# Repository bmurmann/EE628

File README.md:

# EE 628 (University of Hawaiʻi at Mānoa)

### Analysis and Design of Integrated Circuits

Learn mixed-signal circuit design using open-source tools and create your own voltmeter chip!

This course is being developed in collaboration with the Microelectronics Commons [California-Pacific-Northwest AI Hub](https://microelectronicscommons.org/connect/california-pacific-northwest-ai-hardware-hub-northwest-ai-hub/).

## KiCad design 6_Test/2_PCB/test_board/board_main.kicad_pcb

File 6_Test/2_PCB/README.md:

This folder contains all files related to PCB design and test setup.

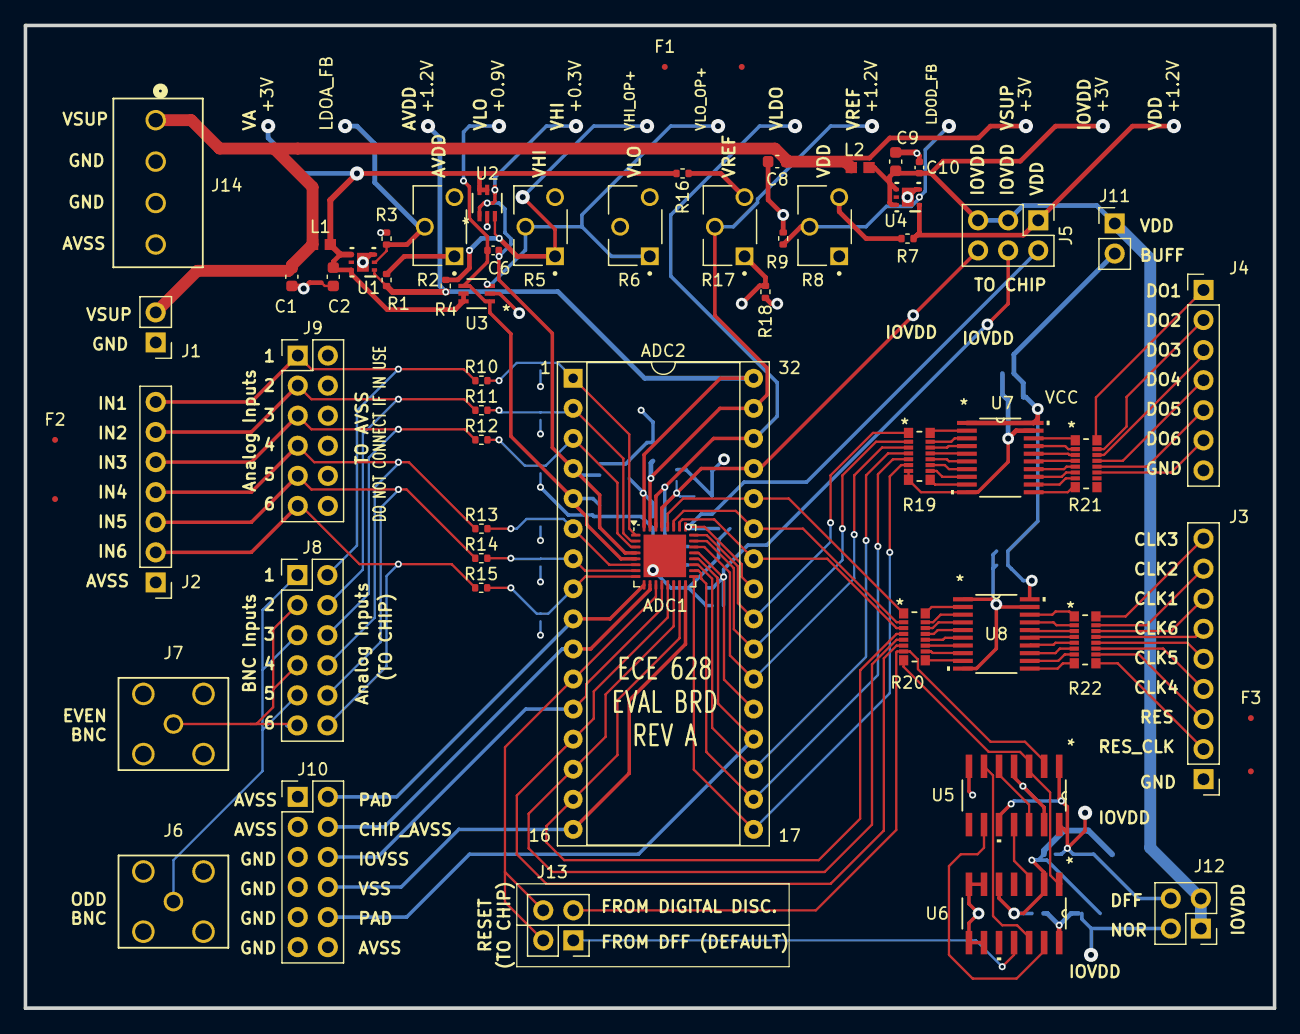
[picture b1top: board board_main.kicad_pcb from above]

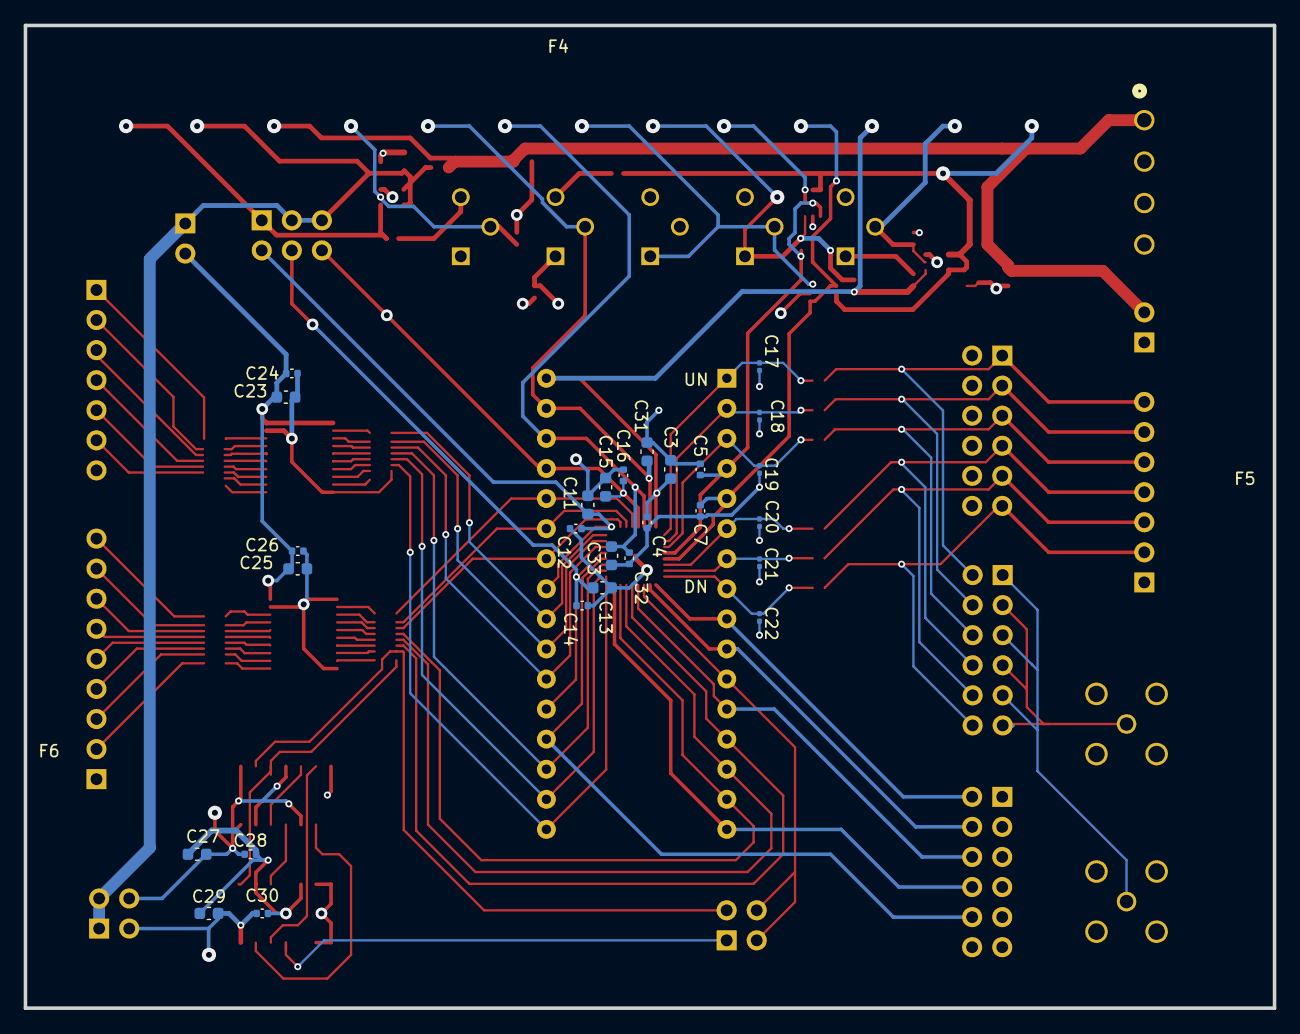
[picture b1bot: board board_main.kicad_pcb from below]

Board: 4 copper layers, 105.5 x 83.0 mm, 87 parts (27 on the bottom side), 110 nets.

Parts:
ADC1: ADC_Chip; QFN-32-1EP_5x5mm_P0.5mm_EP3.6x3.6mm
ADC2: ADC_Socket; DIP-32_W15.24mm_Socket
C1, C2, C3, C8, C9, C11, C13, C15, C23, C25, C27, C29, C31, C33: 4.7u; C_0603_1608Metric
C4, C5, C6, C7, C10, C12, C14, C16, C24, C26, C28, C30, C32: 100n; C_0402_1005Metric
C17, C18, C19, C20, C21, C22: 100pF; C_0201_0603Metric
F1, F2, F3, F4, F5, F6: Fiducial_0.5mm_Mask1.5mm
J1: PWR_Supply_Pins; PinHeader_1x02_P2.54mm_Vertical
J2: Analog_Input_Pins; PinHeader_1x07_P2.54mm_Vertical
J3: Digital_Input_Pins; PinHeader_1x09_P2.54mm_Vertical
J4: Digital_Output_Pins; PinHeader_1x07_P2.54mm_Vertical
J5: Chip_VDD_Jumpers; PinHeader_2x03_P2.54mm_Vertical
J6: BNC_Odd; bnc_mini_gnd
J7: BNC_Even; bnc_mini_gnd
J8: BNC_Jumpers; PinHeader_2x06_P2.54mm_Vertical
J9: Analog_Input_Jumpers; PinHeader_2x06_P2.54mm_Vertical
J10: Chip_AVSS_GND_Jumpers; PinHeader_2x06_P2.54mm_Vertical
J11: Buffer_PWR_Jumper; PinHeader_1x02_P2.54mm_Vertical
J12: Reset_PWR_Jumpers; PinHeader_2x02_P2.54mm_Vertical
J13: Reset_Signal_Jumpers; PinHeader_2x02_P2.54mm_Vertical
J14: 1546551-4; CONN4_1546551-4_TEC
L1, L2: BLM18PG121SN1D; IND_BLM18_0603_MUR
R1, R4, R7, R10, R11, R12, R13, R14, R15: 1k; R_0402_1005Metric
R2, R5, R6, R8, R17: 10k; potentiometer_10turn
R3: r=4.7k; R_0402_1005Metric
R9, R16, R18: 4.7k; R_0402_1005Metric
R19, R20, R21, R22: EXB-2HV220JV; RES_EXB2HV
U1, U4: TPS74501PDRVR; DRV0006A_NV
U2, U3: ADA4807-1AKSZ-R7; KS-6_ADI
U5: SN74HC74DR; flip_flop_D14
U6: CD4001BM96; nor_gate_D14
U7, U8: SN74LVC245APWR; PW20

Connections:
/ADC/AVDD: ADC1.32 (AVDD), ADC2.32 (AVDD), C3.1, C4.2, R1.1, R4.1, U1.1 (OUT)
/ADC/AVSS: C3.2, C4.1, C5.1, C7.1, C17.2, C18.2, C19.2, C20.2, C21.2, C22.2, C31.2, C32.2, C33.2, J2.1, J6.2 (AVSS1), J6.3 (AVSS2), J6.4 (AVSS3), J6.5 (AVSS4), J7.2 (AVSS1), J7.3 (AVSS2), J7.4 (AVSS3), J7.5 (AVSS4), J9.B1, J9.B2, J9.B3, J9.B4, J9.B5, J9.B6, J10.A1, J10.A2, J10.B6, J14.4, R3.1, R6.2, R18.2
/ADC/CK1: ADC1.26 (CK1), ADC2.26 (CK1), R20.3
/ADC/CK2: ADC1.27 (CK2), ADC2.27 (CK2), R20.2
/ADC/CK3: ADC1.28 (CK3), ADC2.28 (CK3), R20.1
/ADC/CK4: ADC1.13 (CK4), ADC2.13 (CK4), R20.6
/ADC/CK5: ADC1.14 (CK5), ADC2.14 (CK5), R20.5
/ADC/CK6: ADC1.15 (CK6), ADC2.15 (CK6), R20.4
/ADC/IN1: J2.7, J8.B1, J9.A1, R10.1
/ADC/IN2: J2.6, J8.B2, J9.A2, R11.1
/ADC/IN3: J2.5, J8.B3, J9.A3, R12.1
/ADC/IN4: J2.4, J8.B4, J9.A4, R13.1
/ADC/IN5: J2.3, J8.B5, J9.A5, R14.1
/ADC/IN6: J2.2, J8.B6, J9.A6, R15.1
/ADC/IOVDD: C9.1, C10.1, J5.1, J5.2, J11.1, J12.1, J12.3, L2.1, U4.4 (EN), U4.6 (IN)
/ADC/OUT1: ADC1.24 (OUT1), ADC2.24 (OUT1), R19.1
/ADC/OUT2: ADC1.23 (OUT2), ADC2.23 (OUT2), R19.2
/ADC/OUT3: ADC1.22 (OUT3), ADC2.22 (OUT3), R19.3
/ADC/OUT4: ADC1.19 (OUT4), ADC2.19 (OUT4), R19.4
/ADC/OUT5: ADC1.18 (OUT5), ADC2.18 (OUT5), R19.5
/ADC/OUT6: ADC1.17 (OUT6), ADC2.17 (OUT6), R19.6
/ADC/RES: ADC1.11 (RES), ADC2.11 (RES), J13.2, J13.4
/ADC/VDD: J5.3, R7.1, U4.1 (OUT)
/ADC/VHI: ADC1.4 (VHI), ADC2.4 (VHI), C5.2, C6.2, U2.1 (VOUT), U2.4 (-IN)
/ADC/VLDO: ADC1.30 (VLDO), ADC2.30 (VLDO), C32.1, C33.1
/ADC/VLO: ADC1.5 (VLO), ADC2.5 (VLO), C6.1, C7.2, U3.1 (VOUT), U3.4 (-IN)
/ADC/VREF: ADC1.31 (VREF), ADC2.31 (VREF), C31.1, R17.2
/AnalogSupply/VA: C2.1, L1.1, R16.1, U1.4 (EN), U1.6 (IN), U2.5 (*DISABLE), U2.6 (+VS), U3.5 (*DISABLE), U3.6 (+VS)
/AnalogSupply/VSUP: C1.1, C8.1, J1.2, J14.1, L1.2, L2.2
/Buffer/CLKX: R20.8, U5.3 (1CLK), U6.1 (A)
/Buffer/CLK_IN1: J3.7, R22.14
/Buffer/CLK_IN2: J3.8, R22.15
/Buffer/CLK_IN3: J3.9, R22.16
/Buffer/CLK_IN4: J3.4, R22.11
/Buffer/CLK_IN5: J3.5, R22.12
/Buffer/CLK_IN6: J3.6, R22.13
/Buffer/CLK_IND: J3.2, R22.9
/Buffer/DO1: J4.1, R21.16
/Buffer/DO2: J4.2, R21.15
/Buffer/DO3: J4.3, R21.14
/Buffer/DO4: J4.4, R21.13
/Buffer/DO5: J4.5, R21.12
/Buffer/DO6: J4.6, R21.11
/Buffer/RESX: J13.1, R20.7, U5.2 (1D)
/Buffer/RES_IND: J3.3, R22.10
/Buffer/VCC: C23.1, C24.1, C25.1, C26.1, J11.2, U7.1 (DIR), U7.20 (VCC), U8.20 (VCC)
GND: ADC1.33 (PADDLE), C1.2, C2.2, C8.2, C9.2, C10.2, C11.2, C12.2, C13.2, C14.2, C15.2, C16.2, C23.2, C24.2, C25.2, C26.2, C27.2, C28.2, C29.1, C30.1, J1.1, J3.1, J4.7, J10.A3, J10.A4, J10.A5, J10.A6, J14.2, J14.3, R9.2, R19.7, R19.8, U1.3 (GND), U1.7 (PAD), U2.2 (-VS), U3.2 (-VS), U4.3 (GND), U4.7 (PAD), U5.7 (GND), U6.2 (B), U6.5 (C), U6.6 (D), U6.7 (VSS), U6.8 (E), U6.9 (F), U7.10 (GND), U7.19 (*OE), U8.1 (DIR), U8.10 (GND), U8.19 (*OE)
unnamed: ADC1.10 (AVSS), ADC2.10 (AVSS), J10.B2
unnamed: ADC1.1 (IN1), ADC2.1 (IN1), C17.1, R10.2
unnamed: ADC1.2 (IN2), ADC2.2 (IN2), C18.1, R11.2
unnamed: ADC1.3 (IN3), ADC2.3 (IN3), C19.1, R12.2
unnamed: ADC1.6 (IN4), ADC2.6 (IN4), C20.1, R13.2
unnamed: ADC1.7 (IN5), ADC2.7 (IN5), C21.1, R14.2
unnamed: ADC1.8 (IN6), ADC2.8 (IN6), C22.1, R15.2
unnamed: ADC1.21 (IOVDD), ADC2.21 (IOVDD), C13.1, C14.1, J5.5
unnamed: ADC1.29 (IOVDD), ADC2.29 (IOVDD), C15.1, C16.1, J5.4
unnamed: ADC1.12 (IOVSS), ADC2.12 (IOVSS), J10.B3
unnamed: ADC1.20 (IOVSS), ADC2.20 (IOVSS), J10.B5
unnamed: ADC1.9 (PAD), ADC2.9 (PAD), J10.B1
unnamed: ADC1.25 (VDD), ADC2.25 (VDD), C11.1, C12.1, J5.6
unnamed: ADC1.16 (VSS), ADC2.16 (VSS), J10.B4
unnamed: J6.1 (Signal), J8.A1, J8.A3, J8.A5
unnamed: J7.1 (Signal), J8.A2, J8.A4, J8.A6
unnamed: R1.2, R2.1
unnamed: R7.2, R8.3
unnamed: R16.2, R17.3
unnamed: R17.1, R18.1
unnamed: R2.2, R3.2, U1.2 (FB)
unnamed: R4.2, R5.1, U2.3 (+IN)
unnamed: R5.2, R6.1, U3.3 (+IN)
unnamed: R8.2, R9.1, U4.2 (FB)
unnamed: U5.5 (1Q), U5.12 (2D)
unnamed: U5.11 (2CLK), U6.3 (J)
unnamed: U5.9 (2Q), U6.13 (H)
unnamed: C27.1, C28.1, J12.2, U5.1 (*1CLR), U5.4 (*1PRE), U5.10 (*2PRE), U5.13 (*2CLR), U5.14 (VCC)
unnamed: U5.6 (*1Q), U6.12 (G)
unnamed: J13.3, U6.11 (M)
unnamed: C29.2, C30.2, J12.4, U6.14 (VDD)
unnamed: R19.16, U7.2 (A1)
unnamed: R19.15, U7.3 (A2)
unnamed: R19.14, U7.4 (A3)
unnamed: R19.13, U7.5 (A4)
unnamed: R19.12, U7.6 (A5)
unnamed: R19.11, U7.7 (A6)
unnamed: R19.10, U7.8 (A7)
unnamed: R19.9, U7.9 (A8)
unnamed: R21.1, U7.18 (B1)
unnamed: R21.2, U7.17 (B2)
unnamed: R21.3, U7.16 (B3)
unnamed: R21.4, U7.15 (B4)
unnamed: R21.5, U7.14 (B5)
unnamed: R21.6, U7.13 (B6)
unnamed: R21.7, U7.12 (B7)
unnamed: R21.8, U7.11 (B8)
unnamed: R20.16, U8.2 (A1)
unnamed: R20.15, U8.3 (A2)
unnamed: R20.14, U8.4 (A3)
unnamed: R20.13, U8.5 (A4)
unnamed: R20.12, U8.6 (A5)
unnamed: R20.11, U8.7 (A6)
unnamed: R20.10, U8.8 (A7)
unnamed: R20.9, U8.9 (A8)
unnamed: R22.1, U8.18 (B1)
unnamed: R22.2, U8.17 (B2)
unnamed: R22.3, U8.16 (B3)
unnamed: R22.4, U8.15 (B4)
unnamed: R22.5, U8.14 (B5)
unnamed: R22.6, U8.13 (B6)
unnamed: R22.7, U8.12 (B7)
unnamed: R22.8, U8.11 (B8)

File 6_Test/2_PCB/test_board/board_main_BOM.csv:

"Id";"Designator";"Footprint";"Quantity";"Designation";"Supplier and ref";
1;"J11";"PinHeader_1x02_P2.54mm_Vertical";1;"Buffer_PWR_Jumper";;;
2;"C24,C6,C30,C7,C14,C37,C16,C34,C10,C4,C28,C26,C12,C32,C5";"C_0402_1005Metric";15;"100n";;;
3;"R10,R1,R13,R14,R7,R4,R11,R15,R12";"R_0402_1005Metric";9;"1k";;;
4;"J9";"2x6Header";1;"Analog_Input_Jumpers";;;
5;"C18,C22,C19,C20,C17,C21";"C_0201_0603Metric";6;"100pF";;;
6;"J7";"bnc_mini_gnd";1;"BNC_Even";;;
7;"J6";"bnc_mini_gnd";1;"BNC_Odd";;;
8;"R27,R20,R25,R29,R18,R16,R21,R28,R17,R26,R19,R24,R23,R22";"R_0402_1005Metric";14;"22";;;
9;"U5";"flip_flop_D14";1;"SN74HC74DR";;;
10;"U6";"nor_gate_D14";1;"CD4001BM96";;;
11;"U7";"DL56";1;"SN74ALVCH162827DLR";;;
12;"J13";"2x2Header";1;"Reset_Signal_Jumpers";;;
13;"R3";"R_0402_1005Metric";1;"r=4.7k";;;
14;"R9,R32,R30";"R_0402_1005Metric";3;"4.7k";;;
15;"L2,L1";"IND_BLM18_0603_MUR";2;"BLM18PG121SN1D";;;
16;"U1,U4";"DRV0006A";2;"TPS74501PDRVR";;;
17;"C3,C9,C2,C27,C35,C25,C29,C13,C36,C23,C33,C1,C8,C31,C15,C11";"C_0603_1608Metric";16;"4.7u";;;
18;"J10";"2x6Header";1;"Chip_AVSS_GND_Jumpers";;;
19;"U3,U2";"KS-6_ADI";2;"ADA4807-1AKSZ-R7";;;
20;"J4";"1x7Header";1;"Digital_Output_Pins";;;
21;"J5";"2x3Header";1;"Chip_VDD_Jumpers";;;
22;"R5,R2,R6,R31,R8";"potentiometer_10turn";5;"10k";;;
23;"J1";"1x2Header";1;"PWR_Supply_Pins";;;
24;"J2";"1x7Header";1;"Analog_Input_Pins";;;
25;"J12";"2x2Header";1;"Reset_PWR_Jumpers";;;
26;"J8";"2x6Header";1;"BNC_Jumpers";;;
27;"J3";"1x9Header";1;"Digital_Input_Pins";;;

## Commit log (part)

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2024-02-11 Added LEC10
2024-02-11 Cleanup
2024-02-14 Added week 6 assignment
2024-02-14 Added LEC11
2024-02-21 Added LEC12
2024-02-21 Added week 7 assignment
2024-02-27 Added week 8 assignment
2024-02-27 Updated schedule
2024-02-28 Updated tool setup
2024-02-28 Added LEC14
2024-02-28 Updated LEC14
2024-03-03 Added week 9 assignment
2024-03-03 Added LEC15
2024-03-03 Added LEC 15
2024-03-06 Updated week 9 assignments
2024-03-06 Added LEC16
2024-03-11 Added LEC17
2024-03-25 Added LEC18
2024-03-25 Added LEC19
2024-03-26 Touch-up
2024-03-26 Added week 12 assignment
2024-03-26 Added ESD paper
2024-03-27 Added IDSM2 postprocessing notebook
2024-03-27 Added LEC20
2024-03-28 Added symbol fix for standard cells & some cleanup
2024-03-29 Updated tb_IDSM2.ipynb
2024-03-29 Added LEC21
2024-04-03 Added tb_stage_corners notebook
2024-04-03 Added LEC22
2024-04-07 Added LEC23
2024-04-09 clean
2024-04-09 another
2024-04-09 comm
2024-04-09 Added week 14 assignment
2024-04-09 Added LEC24
2024-04-09 Updated week 14 assignment
2024-04-10 Add clock generator file
    This is an initial layout for the clock generator for the IDSM2.
2024-04-15 Create Team 6
    Upload Layout
2024-04-15 Create Layout
2024-04-15 Team 1 latest layout
    The latest versions of the clock generator, comparator, and stage layouts.
    The clock generator was recreated to be more compact.
2024-04-15 Create folder
2024-04-15 Added week 15 assignment
2024-04-15 added layout for Team Transformer Monster Tractors
2024-04-15 Create Team 4
2024-04-17 Created using Colab
2024-04-21 added io
2024-04-21 updated io
2024-04-22 Added LEC27
2024-04-23 Added LVS setup instructions
2024-04-23 Updated LVS instructions
2024-04-24 added padring schematic
2024-04-24 Added LEC28
2024-04-25 Updated LEC28
2024-04-25 Added padring cell
2024-04-25 Design file cleanup
2024-04-26 Added top level schematic
2024-04-26 Uploaded readme, spice, and symbol
2024-04-26 removed notebook
2024-04-26 Uploaded updated spice and sim files
    Updated according to Lecture 28
2024-04-27 Schematic update
2024-04-27 Update Team 1 submission
2024-04-27 Updated padring
2024-04-27 Update _sim file to have correct format
2024-04-27 uploaded team2 layout files
2024-04-27 Delete 5_Design/4_Layout/Team 4/stage_2024_04_13.oas
    Removing unwanted file to avoid confusion.
2024-04-28 added files to submit
2024-04-28 Rename Team5.readme to Team5.readme.md
2024-04-28 fixed IHPcell bug
2024-04-28 Updated layout
2024-04-28 Correct pins on comparator
    • Swapped vdda and vssa pins on comparator in IDSM2_t1 schematic
    • Swapped p1 and res pins on comparator in IDSM_t1 schematic
    • Reordered IDSM2_t1 pin in Team1.spice file to match Team1_sim.spice file
2024-04-29 Updated hacks
2024-04-29 Team5 Integration into testbench and top-level schematic. Testbench netlists and runs transient operating point successfully. [schematic]
2024-04-30 Updated IO cells (analog pad passes LVS now)
2024-04-30 Updated team 6 & debug
2024-05-01 Fixed inv pin order in stdcell cdl
2024-05-02 Progress with IDSM2 layout
2024-05-03 Updated top-level layout
2024-05-03 Added week 16 assignment
2024-05-03 Updated padring schematic and symbol
2024-05-03 Add files via upload
    Final files for EE 628 (Layout is DRC and LVS clean). Cheers!
2024-05-03 Rename Team4_sim (1).spice to Team4_sim.spice
2024-05-04 Updated top level symbol and schematic for VSS changes. (Removed iovss and avss and added an annotated short at the top level of these three nets). Also modified testbench for pwl clock files.
2024-05-04 Added DC op conditions
2024-05-04 Final update of Team 1 layout
2024-05-04 Updated Team2 Files
2024-05-04 Inverter under mimcap lvs test
2024-05-04 Inverter drive strength test bench. Dubugging needed on main circuit but 1x inverter driving 1pF load with 25MHz square wave with 1ns rise/fall time is simulated.
2024-05-05 Updated top layout (Teams 3+4 LVS clean)
2024-05-05 Updated LVS hack documentation
2024-05-05 updated files, added ML notebook
2024-05-05 updated files
2024-05-05 Team2 test
2024-05-06 Team2 integrated into top testbench and netlisting.
2024-05-06 Updated readme/spice/sym files
2024-05-06 Updated top layout (Team2 added, DRC/LVS clean)
2024-05-06 Modified subcircuit header back to Team1
2024-05-07 Fixed VDD pad bug
2024-05-07 Team 1 debugging, some twekas, but two shorts remain to be fixed
2024-05-08 Fixed the PR and Res short
    PS now has the correct connections and is not shorted with RES, The inverter VDD has been fixed to connect to the D Flip-Flop VDD which is connected to VDD.
2024-05-08 Initial version of density monitor check. Characterizes global density of M1-M5 in steps of [start=10:end=50:step=5]. density_gen_script.py used to create density checks for .lydrc file.
2024-05-08 Added some basic testbenches for public consumption
2024-05-08 Updated Team 1 oas file
2024-05-08 Approximately 80-90% LVS clean
    Some weird issues with DRC fussing about via 2 sizes, even though they are 0.19x0.19 and with a topmetal1.drawing that says min width of 1.64 but the width is 1.64. Much more LVS checks out, mainly i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
2024-05-08 Fixed any via issues that I could find
2024-05-08 Top layout update (integrated Team1, DRC & LVS clean)
2024-05-09 Updated top layout with guard rings (DRC & LVS clean)
2024-05-10 final layout
2024-05-10 Top cdl update
2024-05-10 Partial update of top layout
2024-05-10 Fill files to be imported into chip top.
2024-05-10 Top level updated (Team 5 integrated & LVS clean)
2024-05-10 Re-netlisted with updated symbols
2024-05-10 Updated as a subcircuit
2024-05-10 Updated with padring instance
2024-05-10 Updated Team5 symbol to correct format and regenerated top netlist
2024-05-10 revised layout
2024-05-10 updated notes in readme
2024-05-10 removed line talking about layers bug. It was handled
2024-05-10 Updated LVS netlist to reflect Team4 global VSS
2024-05-10 Updated top layout (update Team 5, new netlist from schematic dir LVS clean)
2024-05-10 Updated fills to drawing layers from filler layers
2024-05-10 Combined fill file in the oasis format converted from gds
2024-05-10 Updated top layout with fill (LVS clean)
2024-05-11 Updated with seal ring
2024-05-11 LVS hack to pass with sealring, some clean-up
2024-05-11 Updated top layout (team 1 fixes, Team 5 updated layout, added M2 in padring corner), LVS clean with sealring
2024-05-11 Updated top layout (checked with sg13g2-minimal.lydrc, made contact size fixes to Team1.oas, DRC & LVS clean).
2024-05-12 Updated Team_2.oas file
2024-05-12 Updated top layout (improved Team2 layout, still needs fill update)
2024-05-12 Updated top layout (LVS clean wihtout fill cell)
2024-05-12 TV1 enclosure by metal 5 changes
2024-05-12 TV1 enclosure by metal 5 changes - metal 5 adjustment
2024-05-13 Adjusted TV1 + TopMetal1 proximity to Team2 design at coordinates 557.215 x 824.81
2024-05-13 Updated fill pattern for Team2 revisions
2024-05-13 Clean-up & public sharing of design schematics and simulations
2024-05-14 Create b
2024-05-14 Create temp
2024-05-14 schematic files for Team_2
2024-05-15 Added fill cell - LVS DRC clean
2024-05-15 Updated with current monitors
2024-05-15 Removed floating V1's
2024-05-15 Updated with expanded seal ring - DRC LVS clean
2024-05-15 Added sources to testbench and modified tolerances
2024-05-15 Debugging timestep errors
2024-05-15 gds data for IHP submission
2024-05-15 updated DRC scripts
2024-05-16 Updated fill patterning to <5um. LVS clean. Old rule DRC clean (sg13g2.lydrc)
2024-05-16 Fixed guard ring contacts which were 0.19x0.19 to 0.16x0.16. LVS clean. Old DRC is clean (sg13g2.lydrc)
2024-05-16 Uncompressed format
2024-05-16 schematics
2024-05-17 Upload team 1 schematics
2024-05-19 Updated top layout with new Team2.oas (DRC touch-ups for maximal DRC)
2024-05-22 Updated sealring pycell. LVS clean. DRC improved from earlier sealring pycell errors.
2024-05-22 Updated Team5 design to reduce large vertex polygons in M1. LVS clean. DRC no change.
2024-05-23 Updated Team1.oas (DRC clean with maximal-set, except grid)
2024-05-23 LVS clean - M1 and PSD changes
2024-05-23 PSD and M1 changes - LVS clean
2024-05-23 M1 errors clean - LVS clean
2024-05-23 M2 fixed - LVS clean
2024-05-23 DRC LVS clean (DRC offgrid errors still in design)
2024-05-23 Contact rules cleaned. LVS clean
2024-05-23 M2, M3, M4 area violations cleared. LVS clean
2024-05-23 Some PSD fixed
2024-05-23 More PSD fixes. LVS clean
2024-05-23 LVS Clean. DRC Clean (except for off-grids).
2024-05-23 LVS clean. DRC clean (except for off-grid errors)
2024-05-23 Updated padring (fixed some DRC errors flagged by the maximal deck & addressed a few grid errors. Top is LVS clean).
2024-05-24 Updated Team_2.oas and Team_2.spice
    I updated the layout splitting the capacitor into 6 smaller capacitors to pass the DRC. It only passes LVS when I keep the same-sized capacitor in the schematic with 6 fingers, so I had to update the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
2024-05-24 Top layout & Team1 update (Team1 is now on grid, top os LVS clean).
2024-05-24 Updated top layout (Team2 cell with split MIM; top is LVS clean, remaining DRC errors are off-grids & fill)
2024-05-24 Updated LDO schematic
    The capacitor is updated to match the LVS
2024-05-24 Updated Team_2_sim.spice
2024-05-24 Checking in off-grid fixing script. Modified to snap pin layers.
2024-05-25 Layout file copy prior to fixing off-grids (with Hierarchy)
2024-05-25 DRC LVS clean files
    Uploaded Team_2.oas - LVS/DRC clean, Team_2_UNFLAT.oas - LVS clean and few offgrid DRC errors, Team2_logo.oas - DRC Clean
2024-05-25 Copied from Team directory
2024-05-25 LVS Clean. DRC Clean (besides density and waived recommended rules)
2024-05-25 Fill as a separate gds
2024-08-03 Added Test folders
2024-08-28 Added bonding diagram
2024-08-29 Added pin list.
2024-08-30 initial kicad project. includes symbols and footprints for all ICs
2024-08-31 added footprints and symbols for other passive parts
2024-09-02 added potentiometer model. Split up design into sheets. Progress on analog power supply
2024-09-06 progress on analog supply. added ferrite beads
2024-09-17 backups and testing lone schematics
2024-09-18 Digital schematic sheets
2024-09-23 ldo simulations done
2024-09-24 progress on op amp. ldo done
2024-10-25 Updated board schematic
    Integrating the power supplies on separate sheets. Includes the ADC chip and socket and connecting circuitry.
2024-11-01 Lock removed
2024-11-07 op amps done simulating
2024-11-07 analog supply complete
2024-11-07 analog final complete
2024-11-09 Added simulation for digital power supplies and buffer
2024-11-09 added jumper lib and reset pulse
2024-11-13 creating new project. combining work
2024-11-14 Fixed simulation models
    Consolidated simulation libraries into sim_models folder in my simulations folder and adjusted file names to be relative paths
2024-11-14 progress on merging
2024-11-14 fixed digital supply, added three sheets to board main
2024-11-15 Clean up folder
2024-11-16 Digital Buffer Simulation
2024-11-20 final draft of board done.
2024-11-20 renamed directories. only using test_board and left all other scratch work in test_board_reference
2024-11-20 fixed analog input wires
2024-11-21 Corrections to schematic 11_20_24
2024-11-21 Remove lock
2024-11-25 made changes with accordance to feedback. Remvoed excess files.
2024-11-26 Edits 112524
2024-11-27 Revert "Corrections to schematic 11_20_24"
2024-11-27 final draft of board, revision 2
2025-01-27 Edit Layout 1_27
    Rearranged the components in the layout and added majority of traces and ground layer. AVSS connections still need to be connected along with IOVDD
2025-02-04 Finished board layout
2025-02-04 Refining board layout & 3D model
2025-02-04 Fixed DRC errors
2025-02-07 Board Edits 250206
    - Added the terminal block (4 positions - VSUP, GND, GND, & AVSS)
    - Added vias for test points
    - Added silkscreen labels for all inputs, jumpers, and potentiometers
    - Widened traces going across the board
    - Relabeled plane as AVSS plane
    - Fixes to 3D model of board
2025-02-07 Adjusted potentiometers
    Equally spaced potentiometers & added additional silkscreen
2025-02-13 updated BOM
2025-02-19 fixed overlapping net issues on final revision
2025-02-19 fixed drc errors, refilled zones, generated gerber files
2025-02-19 added drill and centroid files
2025-04-02 zipped fab files
2025-05-14 added test scripts
2025-07-30 Added chip photos, clean-up
2025-07-30 Added thesis
